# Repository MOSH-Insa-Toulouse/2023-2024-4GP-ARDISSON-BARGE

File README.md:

# 4GP 2023/2024 - Projet de capteur _low-tech_ en graphite - Par Cyril ARDISSON et Kévin BARGE <br>

## Table des matières
✓ [Contacts](#contacts) <br>
✓ [Contexte](#contexte) <br>
✓ [Livrables](#livrables) <br>
✓ [Matériel requis](#matériel-requis) <br>
[1- Simulation sous LTSpice](#1--simulation-sous-ltspice) <br>
[2- Design du PCB sous KiCAD](#2--design-du-pcb-sous-kicad) <br>
[3- Code sous Arduino IDE](#3--code-sous-arduino-ide) <br>
[4- Application Android](#4--application-android) <br>
[5- Réalisation du shield](#5--réalisation-du-shield) <br>
[6- Banc de test et principaux résultats](#6--banc-de-test-et-principaux-résultats) <br>
[7- Datasheet du capteur](#7--datasheet-du-capteur) <br>
✓ [Conclusions et analyse critique du projet](#conclusions-et-analyse-critique-du-projet) <br>
___
## Contacts
Cyril ARDISSON : [ardisson@insa-toulouse.fr](mailto:ardisson@insa-toulouse.fr) <br>
Kévin BARGE : [barge@insa-toulouse.fr](mailto:barge@insa-toulouse.fr) <br>
___
## Contexte
Dans le cadre de l'UF de 4ème Année spécialité Génie Physique "Du capteur au banc de test" (I4GPMH21), nous avons réalisé l'évaluation d'une technologie low-tech : un capteur en graphite, composé de papier, recouvert d'une couche de graphite qu'on peut simplement trouver dans les crayons à papier ! En se déformant, le nombre de particules de graphite reliées varie, ce qui entraîne une modification de sa résistance. De cela, on peut donc induire la déformation. Sur le même principe qu'une jauge de contrainte (ici low-tech !). Ce travail se base sur les travaux de chercheurs de l'Université de Northwestern (Etats-Unis), publiés en 2014 dans l'article "_Pencil Drawn Strain Gauges and Chemiresistors on Paper_" (Cheng-Wei Lin, Zhibo Zhao, Jaemyung Kim & Jiaxing Huang). 

Afin de réaliser ce projet, plusieurs étapes ont été réalisées : simulation électronique, design de PCB et fabrication, programmation d'un Arduino Uno et d'une IHM, mise en place d'un banc de test et écriture d'une datasheet.

Ici, nous faisons le tour de tout ce qui a été fait dans le cadre de ce projet.

___
## Livrables
Plusieurs livrables sont attendus :

✓ **Le shield PCB connecté à une carte Arduino Uno**, composé : du capteur en graphite, d'un montage amplificateur transimpédance et d'un module Bluetooth. D'autres composants peuvent aussi être implémentés (*) : écran OLED, encodeur rotatoire, potentiomètre digital, flex sensor et connexions pour un servo-moteur ; <br>
✓ **Le code Arduino** permettant d'effectuer les mesures du capteur et de contrôler les composants implémentés ; <br>
✓ **L'APK Android** permettant d'interfacer le shield et le code Arduino correspondant : l'IHM en résumé ; <br>
✓ **Le / Les code(s) Arduino** permettant d'effectuer les tests du capteur ; <br>
✓ **La datasheet du capteur** reprenant toutes ses caractéristiques ainsi que ses tests. <br>

(*) Pour notre projet, nous avons décidés d'implémenter sur notre shield : l'écran OLED, l'encodeur rotatoire, le potentiomètre digital et le flex sensor. 
___
## Matériel requis
Afin de réaliser notre dispositif, nous avons eu besoin de :

Pour le montage amplificateur transimpédance : <br>
✓ Résistances : une de $1\ \text{k}\Omega$, une de $10\ \text{k}\Omega$ et deux de $100\ \text{k}\Omega$ - une troisième de $100\ \text{k}\Omega$ peut être prévue, mais peut aussi être substituée par une résistance variable (le potentiomètre digital), choix que l'on a fait ; <br>
✓ Un potentiomètre digital (si substitution d'une résistance de $100\ \text{k}\Omega$) : ici, choix du MCP41050 ; <br>
✓ Capacités : trois de $100\ \text{nF}$ et une de $1\ \mu\text{F}$ ; <br>
✓ Un amplificateur opérationnel : ici, choix du LTC1050 ; <br>

Pour le reste du dispositif : <br>
✓ Un module Bluetooth : ici, choix du HC05 ; <br>
✓ Un écran OLED de dimension 128*64 ; <br>
✓ Un encodeur rotatoire ; <br>
✓ Un flex sensor.
___
## 1- Simulation sous LTSpice
Notre capteur en graphite a une résistance de l'ordre du ${G}\Omega$, ce qui conduit, en appliquant une tension d'entrée de $5\ \text{V}$, à obtenir un courant de quelques ${nA}$. En conséquence, notre Arduino Uno ne pourra pas le lire. Il y a donc nécessité d'amplifier ce signal : c'est donc ce pourquoi nous mettons en place un **montage amplificateur transimpédance**. <br>

**_Description du montage amplificateur transimpédance_** <br>
Notre montage est composé de 4 zones importantes, une pour l'amplification et trois qui correspondent à des filtres : <br>
✓ Un premier filtre en entrée de l'amplificateur (${R1}$ et ${C1}$) : il correspond à un filtre passe-bas, qui permet de filtrer le bruit en courant sur le signal d'entrée ; <br>
✓ Un second filtre couplé à l'amplificateur (${R3}$ et ${C4}$) : il correspond aussi à un filtre passe-bas, qui permet de filtrer la composante 50 Hz du réseau électrique ; <br>
✓ et un troisième filtre en sorti de l'amplificateur (${R6}$ et ${C2}$) : pour filtrer le bruit lié au traitement opéré par l'amplificateur. <br>

<br>

Sur LTSpice, nous avons testé ce montage en deux temps. <br>

**_Simulations réalisées avec LTSpice_** <br>
Sur LTSpice, nous avons testé ce montage en deux temps. <br>

D'abord, nous avons effectué une première simulation pour vérifier si l'amplification était bien effective. Comme on peut le constater ci-dessous, le signal est bien amplifié à $1\ \text{V}$ : l'Arduino pourra donc l'interpréter. <br>

<br>

Enfin, nous avons effectué une seconde simulation, afin d'observer la réponse à un courant alternatif et ainsi de vérifier que le signal est bien filtré. Comme on peut aussi le constater ci-dessous, le signal paraît filtré, successivement par les 3 filtres. <br>

<br><br>
___
## 2- Design du PCB sous KiCAD
Ici, nous sommes repartis du montage décrit ci-dessus, avec quelques modifications et ajouts de composants. Nous avons utilisé le logiciel KiCad 7.0 : <br>
✓ Comme mentionné auparavant, nous avons remplacé ${R2}$ par le potentiomètre digital ; <br>
✓ Ajout d'un module Bluetooth afin d'assurer la communication entre le PCB et l'APK Android ; <br>
✓ Ajout d'un écran OLED afin d'afficher 3 menus différents ; <br>
✓ Ajout d'un encodeur rotatoire afin de passer de menu en menu ; <br>
✓ Et enfin, ajout d'un flex sensor, en vu des tests finaux. <br>

Pour se faire, nous avons débuté par la création de notre propre bibliothèque de symboles correspondant à nos composants. Puis, nous avons procédé à la création de la schématique électrique de l'ensemble du montage. L'image ci-dessous correspond à cette schématique. <br>

 <br>

Puis, nous avons créé les empreintes de nos composants, en respectant certaines dimensions, en vu de l'impression du PCB (diamètre des trous, forme des empreintes, etc.). Nous sommes ensuite passés à la disposition des composants sur le PCB : une étape fastidieuse avec des compromis afin d'obtenir le placement le plus efficace (en considérant les connexions entre composants, en évitant d'avoir recours aux vias, etc.)... L'image ci-dessous correspond au résultat final de notre PCB, et sa vue en 3D correspondante :

 <br>

Les fichiers KiCad sont disponibles dans le dossier [KiCad](https://github.com/MOSH-Insa-Toulouse/2023-2024-4GP-ARDISSON-BARGE/tree/main/KiCad). 
___
## 3- Code sous Arduino IDE
Le code de contrôle, qui permet d'effectuer les mesures du capteur et de contrôler les composants implémentés, a été développé sous Arduino IDE 2.3.2. <br>

Pour communiquer en Bluetooth, nous avons utilisé la bibliothèque _SoftwareSerial.h_ et pour contrôler l'écran OLED, la bibliothèque _Adafruit_SSD1306.h_. <br>

Notamment, en plus de la communication Bluetooth entre notre PCB et l'application Bluetooth, notre code permet de contrôler deux menus à afficher sur l'écran OLED : <br>
✓ Un menu pour afficher la résistance du capteur _en direct_ ; <br>
✓ Et un menu pour afficher la résistance du flex sensor _en direct_. <br>

Les mesures se font toutes les 100 ms. <br>

Le code complet est disponible [ici](https://github.com/MOSH-Insa-Toulouse/2023-2024-4GP-ARDISSON-BARGE/blob/main/ArduinoIDE/ARDISSON-BARGE_CodeFinal.ino). <br>
___
## 4- Application Android
Nous avons créé une application en guise d'interface, avec MIT App Inventor. <br>

 <br>

Cette application se veut simple et permet : <br>
✓ De se connecter au module Bluetooth du PCB afin de communiquer avec ce dernier ; <br>
✓ D'afficher sur un graphe la résistance du capteur en fonction du temps (où on peut démarrer / arrêter l'acquisition + effacer le graphe) ; <br>
✓ Et d'afficher la résistance "en direct". <br>

_Néanmoins, on rencontre tout de même quelques problèmes de connexion entre l'app qu'on installe sur un smartphone Android et le module Bluetooth. Bien souvent, aucune donnée n'est récupérée._ <br>

L'application est disponible [ici](https://github.com/MOSH-Insa-Toulouse/2023-2024-4GP-ARDISSON-BARGE/blob/main/MITAppInventor). <br>
___
## 5- Réalisation du shield
Fin mars, nous avons pu passer à la réalisation _physique_ de notre PCB. Voici les étapes de fabrication réalisées, avec l'aide de Cathy Crouzet (_merci !_) : <br>

Étape 0 (_importante !_) : vérification du PCB sous KiCad, notamment test DRC <br>
Étape 1 : édition du masque de gravure sous KiCad <br>
Étape 2 : insolation UV d'une plaquette d'époxy (recouverte d'une couche de cuivre et de résine photosensible) <br>
Étape 3 : immersion de la plaquette dans un révélateur afin d'éliminer la résine non-insolée <br>
Étape 4 : immersion de la plaquette dans du perchlorure de fer pour graver les pistes <br>
Étape 5 : nettoyage de la plaquette avec de l'acétone pour retirer la résine restante <br>
Étape 6 : perçage des trous et placement des composants sur le PCB <br>

L'image ci-dessous illustre le rendu final de notre PCB : <br>

 <br>
___
## 6- Banc de test et principaux résultats
Afin de tester nos capteurs, nous avons utilisés le banc de test suivant, composé de 7 demi-cercles, avec des diamètres de 2 à 5 cm (0,5 cm d'écart entre chaque). <br>

 <br>

Ce banc de test nous permet d'obtenir la variation de résistance $\frac{\Delta R}{R_0}$ en fonction de la déformation $\epsilon = \frac{e}{D}$ avec $e$ l'épaisseur du capteur (ici 0,2 mm) et $D$ le diamètre du cercle considéré. <br>

Nous avons réalisé les tests en *compression* et en *tension*. <br>

 <br>

Nous avons effectués les tests avec des capteurs recouverts de deux types de graphite différents : d'un crayon HB et d'un crayon 2B. (*) <br>

Voici les caractéristiques en compression : <br>
 <br>

Et les caractéristiques en tension : <br>
 <br>

On peut donc remarquer que la résistance diminue lorsqu'on augmente la compression, alors que la résistance augmente lorsqu'on augmente la tension. Ceci semble cohérent : en compression, la distance entre les atomes diminue et donc la résistance dimunue en conséquence. L'inverse est vrai en tension. <br>

De plus, on voit qu'avec un crayon plus gras (2B étant plus gras que HB - plus de carbone !), la variation relative de résistance est moins importante. 

Enfin, pour comparer, nous avons aussi réalisé le test en tension (car cela ne fonctionne pas en compression !) avec le flex sensor : <br>
 <br>

On remarque donc que, en comparaison de nos capteurs, le flex sensor semble plus sensible, ce qui semble faire sens. Pour des déformations importantes, il semble aussi être plus apte à les tolérer, "plus solide". <br>

(*) _Nous voulions aussi tester notre capteur en graphite issu d'un crayon B, mais les tests n'étaient pas concluants. En effet, cette méthode de test donne des résultats assez aléatoirement. L'usage d'un servomoteur avec une inclinaison pas à pas sur les demi-cercles pourrait peut-être donner des résultats plus stables. Dans la même optique, une méthode de contrôle de la quantité de graphique déposée sur les capteurs serait la bienvenue, étant assez aléatoire. Tout cela conduit donc à avoir, en l'état, des conditions de test assez peu reconductibles._ <br>
___
## 7- Datasheet du capteur
La datasheet de notre capteur est disponible [ici](https://github.com/MOSH-Insa-Toulouse/2023-2024-4GP-ARDISSON-BARGE/blob/main/Datasheet/ARDISSON-BARGE_Datasheet.pdf).  <br>
___
## Conclusions et analyse critique du projet
Ce projet a été très enrichissant, nous donnant une réelle perspective du travail de l'ingénieur, en le conduisant de bout en bout, des simulations à la datasheet. On a pu avoir avoir une bonne perspective d'une variété de compétences (simulation électronique, développement informatique, design d'un montage électronique, fabrication _physique_ de ce dernier, etc.). En ce sens, c'est donc assez professionnalisant, et gratifiant d'avoir un produit final. <br>

En ce qui concerne le capteur produit, il est fonctionnel et les tests nous permettent de dégager des tendances cohérentes avec la physique. Néanmoins, comme souligné plus haut, les conditions de tests sont rudimentaires et peu reproductibles, ce qui conduit à tout de même obtenir des résultats assez aléatoires. Il faut donc prendre du recul. <br>

Maintenant, il est clair que dans un objectif pédagogique, ce projet est idéal ! <br>

_En espérant que notre société GazouTech va prospérer grâce à ce dernier !_ <br>

<br>

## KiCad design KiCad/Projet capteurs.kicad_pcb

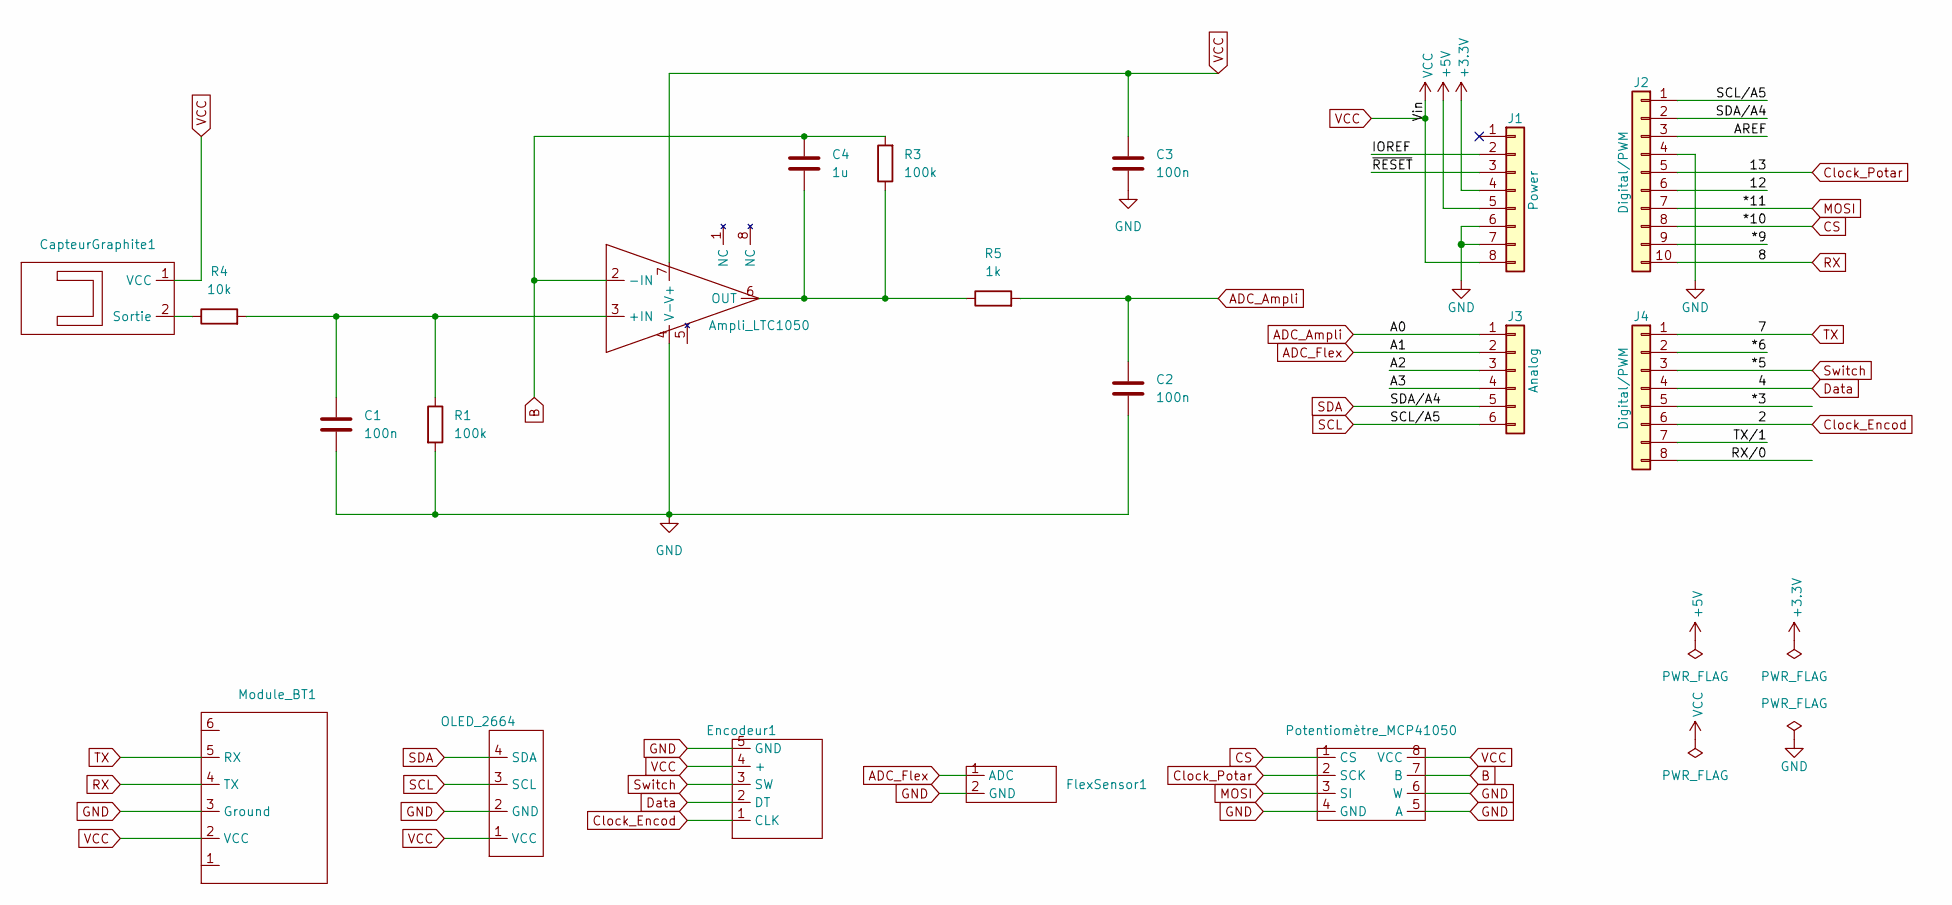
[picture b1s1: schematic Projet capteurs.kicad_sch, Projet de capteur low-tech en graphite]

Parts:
Ampli_LTC1050: Ampli_LTC1050
C1, C2, C3: 100n; C_Radial_D5.0mm_H7.0mm_P2.00mm
C4: 1u; C_Rect_L4.6mm_W2.0mm_P2.50mm_MKS02_FKP02
CapteurGraphite1: CapteurGraphite
Encodeur1: Encodeur
FlexSensor1: FlexSensor
J1: Power; PinSocket_1x08_P2.54mm_Vertical
J2: Digital/PWM; PinSocket_1x10_P2.54mm_Vertical
J3: Analog; PinSocket_1x06_P2.54mm_Vertical
J4: Digital/PWM; PinSocket_1x08_P2.54mm_Vertical
Module_BT1: Module_BT_new
OLED_2664: OLED_2864
Potentiomètre_MCP41050: MCP41050
R1, R3: 100k; R_Axial_DIN0207_L6.3mm_D2.5mm_P7.62mm_Horizontal
R4: 10k; R_Axial_DIN0207_L6.3mm_D2.5mm_P7.62mm_Horizontal
R5: 1k; R_Axial_DIN0207_L6.3mm_D2.5mm_P7.62mm_Horizontal

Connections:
+3V3: J1.4
+5V: J1.5
/12: J2.6
/*3: J4.5
/*6: J4.2
/*9: J2.9
/A2: J3.3
/A3: J3.4
/AREF: J2.3
/IOREF: J1.2
/RX/0: J4.8
/TX/1: J4.7
/~RESET: J1.3
ADC_Ampli: C2.1, J3.1, R5.2
ADC_Flex: FlexSensor1.1 (ADC), J3.2
B: Ampli_LTC1050.2 (-IN), C4.1, Potentiomètre_MCP41050.7 (B), R3.2
CS: J2.8, Potentiomètre_MCP41050.1 (CS)
Clock_Encod: Encodeur1.1 (CLK), J4.6
Clock_Potar: J2.5, Potentiomètre_MCP41050.2 (SCK)
Data: Encodeur1.2 (DT), J4.4
GND: Ampli_LTC1050.4 (V-), C1.2, C2.2, C3.2, Encodeur1.5 (GND), FlexSensor1.2 (GND), J1.6, J1.7, J2.4, Module_BT1.3 (Ground), OLED_2664.2 (GND), Potentiomètre_MCP41050.4 (GND), Potentiomètre_MCP41050.5 (A), Potentiomètre_MCP41050.6 (W), R1.2
MOSI: J2.7, Potentiomètre_MCP41050.3 (SI)
unnamed: Ampli_LTC1050.3 (+IN), C1.1, R1.1, R4.2
unnamed: Ampli_LTC1050.6 (OUT), C4.2, R3.1, R5.1
unnamed: CapteurGraphite1.2 (Sortie), R4.1
RX: J2.10, Module_BT1.4 (TX)
SCL: J2.1, J3.6, OLED_2664.3 (SCL)
SDA: J2.2, J3.5, OLED_2664.4 (SDA)
Switch: Encodeur1.3 (SW), J4.3
TX: J4.1, Module_BT1.5 (RX)
VCC: Ampli_LTC1050.7 (V+), C3.1, CapteurGraphite1.1 (VCC), Encodeur1.4 (+), J1.8, Module_BT1.2 (VCC), OLED_2664.1 (VCC), Potentiomètre_MCP41050.8 (VCC)

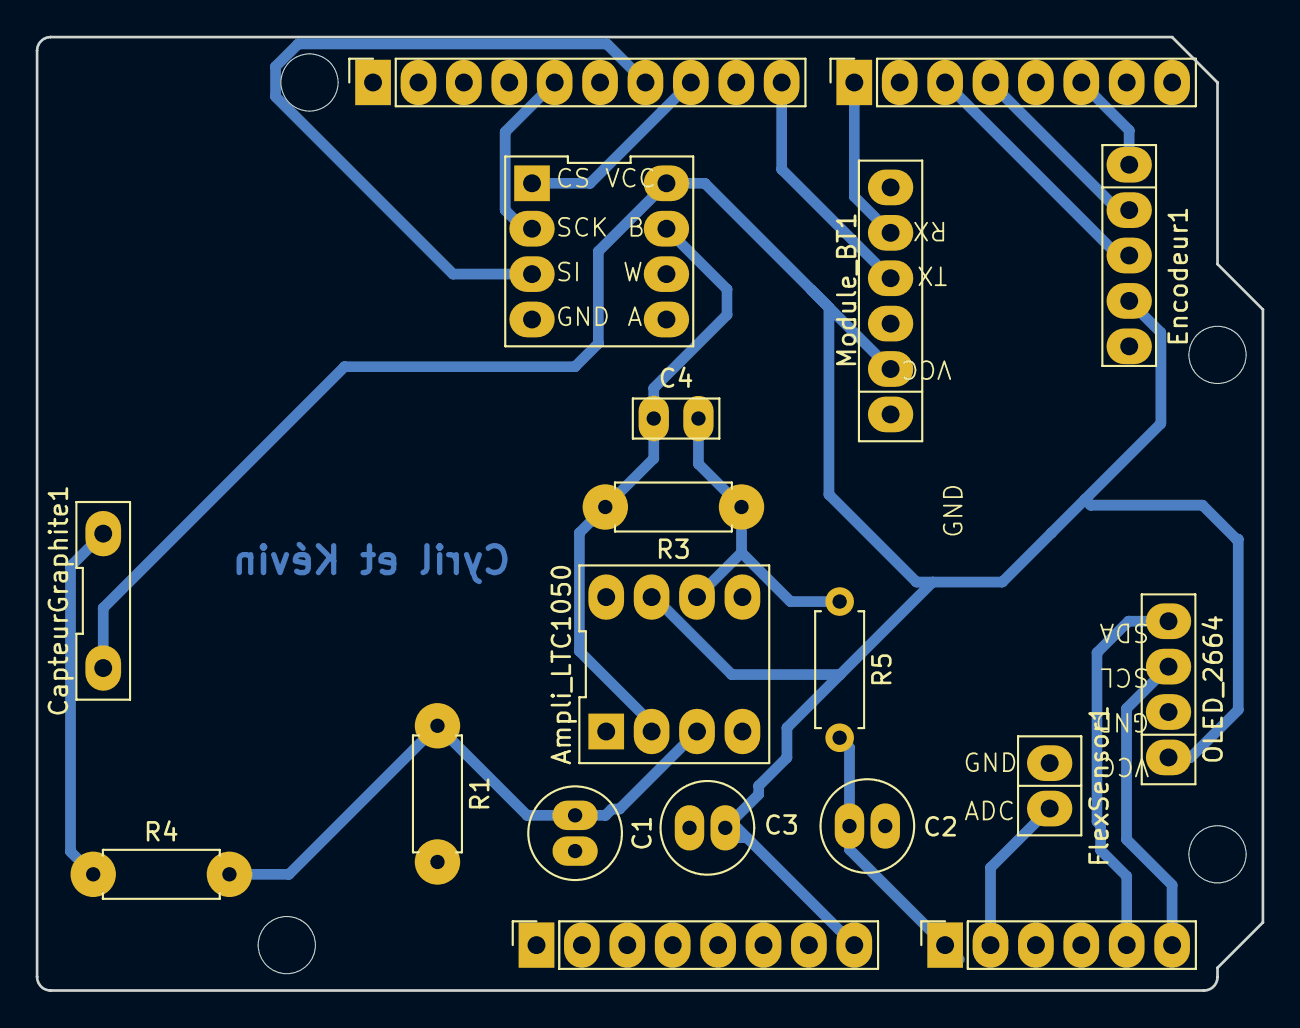
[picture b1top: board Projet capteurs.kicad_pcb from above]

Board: 2 copper layers, 68.6 x 53.3 mm, 23 parts (0 on the bottom side), 18 nets.

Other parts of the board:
MH1, MH2, MH3, MH4: MountingHole_3.2mm
